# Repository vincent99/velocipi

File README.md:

# VelociPi

## About

This runs on a Raspberry Pi 5 to control the screens, cameras, joysticks, audio, and various other toys in my Velocity V-Twin-7 N711ME.

I don't know why you're here, but good luck.

## System setup

### Dependencies

These should be installed on the system:

```
sudo apt install chromium chromium-headless-shell ffmpeg mpv libchromaprint-tools
```

| Binary                           | Package                   | For                                                    |
| -------------------------------- | ------------------------- | ------------------------------------------------------ |
| `chromium-browser` or `chromium` | `chromium`                | Browser for local screen video streaming               |
| `chromium-headless-shell`        | `chromium-headless-shell` | Headless browser for OLED screen                       |
| `ffmpeg`                         | `ffmpeg`                  | DVR recording/streaming, music transcoding             |
| `ffprobe`                        | `ffmpeg`                  | Music duration/metadata extraction (comes with ffmpeg) |
| `mpv`                            | `mpv`                     | Music playback                                         |
| `fpcalc`                         | `libchromaprint-tools`    | Music fingerprinting (optional)                        |

### Hardware config

Enable I2C and SPI interfaces via `raspi-config` (Interface Options)

### Hiding the mouse cursor

Run this once to install a package that will hide the mouse cursor from the local screen

`sudo ./util/install-hideaway.sh`

## Dev

`npm run dev`

## Build

`npm run build`

## Configuration

See `config.yaml`

## WebSocket API

`/ws` carries JSON text frames in both directions (every message has a top-level `type` field). A separate `/screen` endpoint carries only binary PNG frames (the browser screencast) — no JSON messages.

Field-level types live in `ui/src/types/ws.ts` (frontend) and `server/messages.go` / the relevant subsystem's own `messages.go` (backend, e.g. `server/music/messages.go`, `server/dvr/dvr.go`) — this table is a human-readable index, not the source of truth. **Update this table whenever a message type is added, removed, renamed, or changes shape.**

### Server → client

| Type            | Key fields                                                                     | Description                                                       |
| --------------- | ------------------------------------------------------------------------------- | ------------------------------------------------------------------ |
| `ping`          | `time`                                                                           | Periodic heartbeat carrying the server's current time              |
| `airReading`    | `reading` (temp/pressure/humidity/dewpoint, °C+°F)                              | BME280 air sensor reading                                          |
| `luxReading`    | `lux`                                                                            | Ambient light sensor reading                                       |
| `tpms`          | `tire` (position, temp, pressure, voltage, battery, inflation/rotation state)   | One tire pressure sensor reading                                   |
| `ledState`      | `r`, `w`, `b`, `y` (each `{mode, rate?}`)                                        | Full state of all four expander LED channels                       |
| `keyEcho`       | `eventType`, `key`                                                               | Echoes a dispatched key event back to all clients, for UI feedback |
| `cameraStatus`  | `name`, `recording`                                                              | One camera's DVR recording status                                  |
| `recordingReady`| `camera`, `session`, `filename`                                                  | A DVR segment's thumbnails have finished generating                |
| `dvrState`      | `state` (`on`, `paused`, or `off`)                                               | Overall DVR recording state                                        |
| `diskSpace`     | `totalGB`, `usedGB`, `freeGB`, `usedPct`                                         | DVR storage disk space reading                                     |
| `localCamera`   | `camera`                                                                         | Camera currently shown on the local panel display                  |
| `axisState`     | `lat`, `lon`, `altFt`, `heading`, `roll`, `pitch`, `yaw`, `speedKts`, `oatCelsius`| Axis avionics state                                                 |
| `siyiAttitude`  | `camera`, `yaw`, `pitch`, `roll`, `yawRate`, `pitchRate`, `rollRate`             | Siyi gimbal attitude for one camera                                 |
| `musicState`    | `currentSongId`, `queueIndex`, `status`, `shuffle`, `repeat`, `elapsedSec`, `queueLength` | Music player state                                        |
| `musicQueue`    | `currentIndex`, `entries`                                                        | Full music queue snapshot                                          |
| `airConState`   | `state` (mode, fan, setpoint, temps, compressor, error, ...)                     | Aircon controller state                                             |
| `airConHistory` | `history` (array of temp samples)                                               | Temperature history, sent to a client on connect                    |
| `airConSample`  | `sample`                                                                         | One new temperature sample                                          |
| `btDevices`     | `devices` (address, name, paired, connected, trusted)                           | Known classic Bluetooth devices (paired + discovered)                |
| `btNowPlaying`  | `player` (track title/artist/album, status, position) or `null`                  | Current AVRCP now-playing metadata, `null` if no active session      |

### Client → server

| Type              | Key fields                                                  | Description                                                        |
| ----------------- | ------------------------------------------------------------ | -------------------------------------------------------------------- |
| `reload`          | —                                                              | Reload the chromedp browser page                                    |
| `key`             | `eventType`, `key`                                            | Dispatch a logical key event to chromedp / the expander input loop   |
| `led`             | `channel`, `state`, `rate?`                                   | Set one expander LED channel's state                                 |
| `navigate`        | `path`                                                         | Navigate the chromedp browser to a URL path                          |
| `setLocalCamera`  | `camera`                                                       | Change which camera is shown on the local panel display              |
| `musicControl`    | `action` (play/pause/stop/next/prev/seek/...), `value?`, `str?`| Control the music player                                            |
| `btControl`       | `action` (scan/pair/connect/.../playPause/next/previous), `address?` | Control Bluetooth device pairing (`btmedia`) or transport control (`bthid`) |

## Hardware

Display: Generic grayscale [SSD1322 OLED](https://www.amazon.com/dp/B0F7LBQM5N) module (256x64 assumed) or black & white [Noritake-Itron GE256X64B](https://www.noritake-elec.com/products/model?part=GE256X64B-7032B)
Joystick: [RKJXT1F42001](https://www.amazon.com/dp/B0DC623B3S) multi-function switch
Rotary encoder: [Dual concentric](https://www.propwashsim.com/store/p/dual-encoder-kit) with switch
I2C expander: [SX1509](https://www.adafruit.com/product/2260)
I2C air sensors: [BME280](https://www.adafruit.com/product/2652)
I2C light sensor: [VEML6030](https://www.adafruit.com/product/4396)

## Raspberry Pi GPIO pins

| BCM | Physical | Function  | Direction | Connected to                                                         |
| --- | -------- | --------- | --------- | -------------------------------------------------------------------- |
| 2   | 3        | I2C1 SDA  | Bidir     | SX1509 expander, BME280 air sensor, VEML6030 light sensor            |
| 3   | 5        | I2C1 SCL  | Output    | SX1509 expander, BME280 air sensor, VEML6030 light sensor            |
| 5   | 29       | Status/DC | In or Out | OLED status pin (SSD1327: D/C select output; GE256X64B: SBUSY input) |
| 6   | 31       | /RESET    | Output    | OLED reset (active low)                                              |
| 8   | 24       | SPI0 CE0  | Output    | OLED /CS                                                             |
| 10  | 19       | SPI0 MOSI | Output    | OLED data in                                                         |
| 11  | 23       | SPI0 SCLK | Output    | OLED clock                                                           |

I2C address defaults: expander `0x20`, air sensor `0x77`, light sensor `0x48`.
SPI0 port: `/dev/spidev0.0`, default clock `2.40 MHz`.

## SX1509 expander pins

The SX1509 is a 16-bit I2C GPIO expander (pins 0–15). All pins are inputs except the LED (pin 6, output).

| Pin | Function        | Notes                                     |
| --- | --------------- | ----------------------------------------- |
| 0   | Knob center     | Input, active low                         |
| 1   | Inner knob A    | Quadrature encoder (A/B pair with pin 2)  |
| 2   | Inner knob B    |                                           |
| 3   | Outer knob A    | Quadrature encoder (A/B pair with pin 4)  |
| 4   | Outer knob B    |                                           |
| 6   | LED             | Output                                    |
| 8   | Joystick center | Input, active low                         |
| 9   | Joystick down   | Input, active low                         |
| 10  | Joystick up     | Input, active low                         |
| 11  | Joystick right  | Input, active low                         |
| 12  | Joystick left   | Input, active low                         |
| 13  | Joy knob A      | Quadrature encoder (A/B pair with pin 14) |
| 14  | Joy knob B      |                                           |

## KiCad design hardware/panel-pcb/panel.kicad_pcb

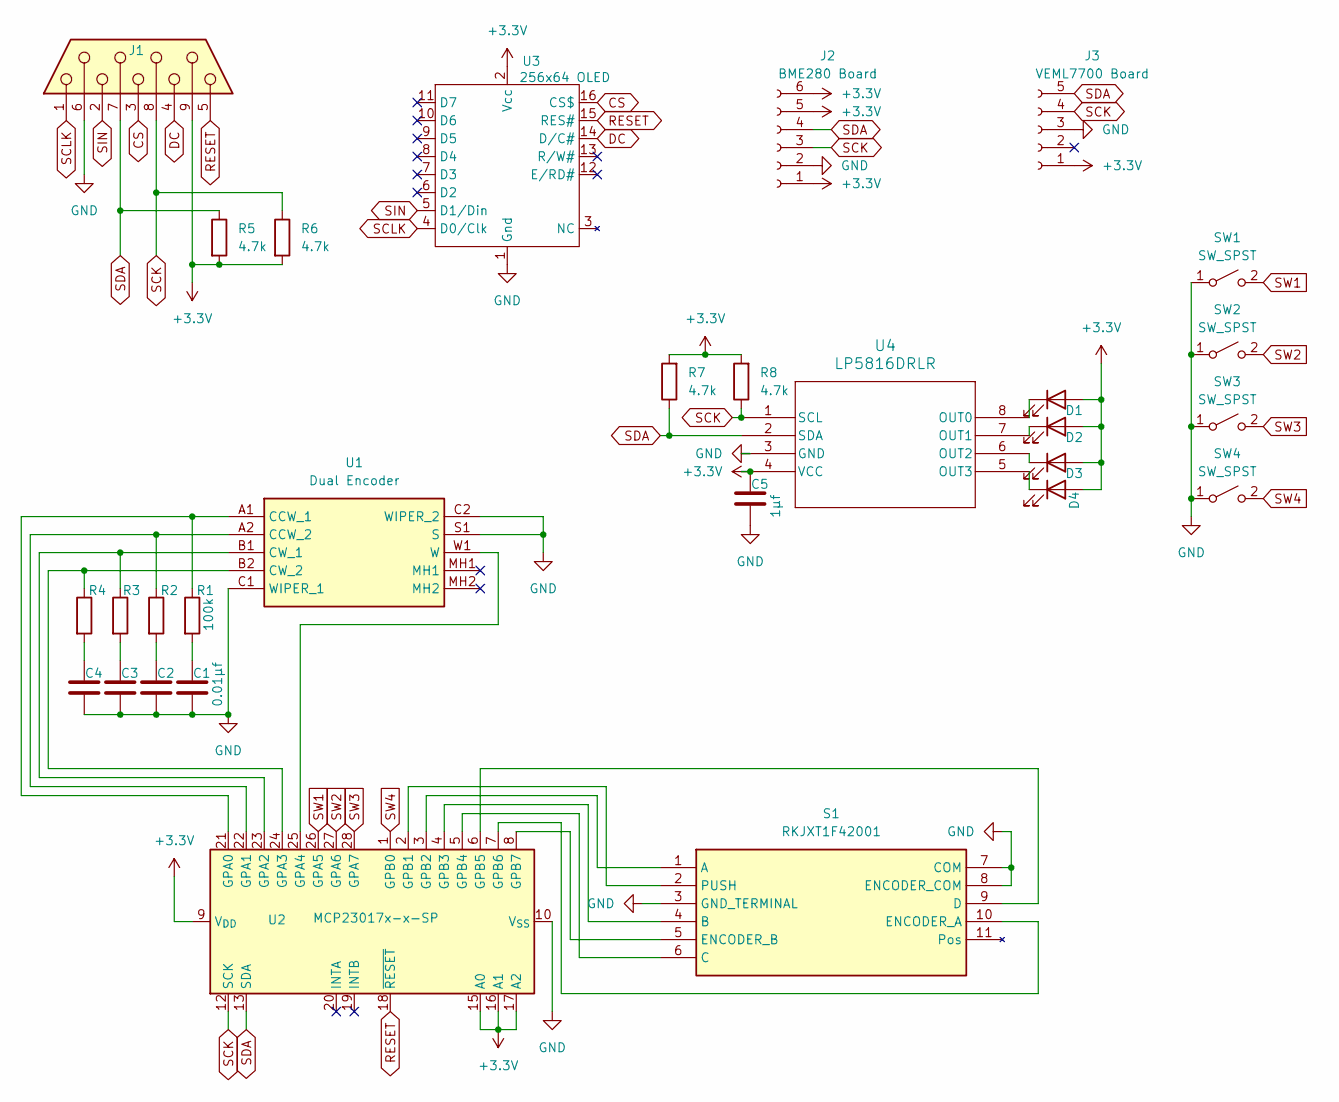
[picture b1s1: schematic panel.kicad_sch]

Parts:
C1, C2, C3, C4: 0.01µf; C_Disc_D5.0mm_W2.5mm_P5.00mm
C5: 1µf; C_Disc_D5.0mm_W2.5mm_P5.00mm
D1: Red; LED_D3.0mm
D2: White; LED_D3.0mm
D3: Blue; LED_D3.0mm
D4: Yellow; LED_D3.0mm
J1: DE9_Socket; DE9 Female
J2: BME280 Board
J3: VEML7700 Board
R1, R2, R3, R4: 100k; R_Axial_DIN0207_L6.3mm_D2.5mm_P7.62mm_Horizontal
R5, R6, R7, R8: 4.7k; R_Axial_DIN0207_L6.3mm_D2.5mm_P7.62mm_Horizontal
S1: RKJXT1F42001; Manufacturer_Part_Number RKJXT1F42001; Mouser Part Number 688-RKJXT1F42001
SW1, SW2, SW3, SW4: SW_SPST; SW_PUSH_6mm_H8mm
U1: Dual Encoder; PEC11D4120FH0015; Mouser Part Number 652-PEC11D4120FH0015
U2: MCP23017x-x-SP; DIP-28_W7.62mm
U3: 256x64 OLED; 3_12_OLED
U4: LP5816DRLR

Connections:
+3.3V: C5.1, D1.2 (A), D2.2 (A), D3.2 (A), D4.2 (A), J1.9, J2.1, J2.5, J2.6, J3.1, R5.2, R6.2, R7.2, R8.2, U2.9 (V_{DD}), U2.15 (A0), U2.16 (A1), U2.17 (A2), U3.2 (Vcc), U4.4 (VCC)
CS: J1.3, U3.16 (CS$)
DC: J1.4, U3.14 (D/C#)
GND: C1.2, C2.2, C3.2, C4.2, C5.2, J1.6, J2.2, J3.3, S1.3 (GND_TERMINAL), S1.7 (COM), S1.8 (ENCODER_COM), SW1.1 (A), SW2.1 (A), SW3.1 (A), SW4.1 (A), U1.C1 (WIPER_1), U1.C2 (WIPER_2), U1.S1 (S), U2.10 (V_{SS}), U3.1 (Gnd), U4.3 (GND)
unnamed: C1.1, R1.2
unnamed: C2.1, R2.2
unnamed: C3.1, R3.2
unnamed: C4.1, R4.2
unnamed: D1.1 (K), U4.8 (OUT0)
unnamed: D2.1 (K), U4.7 (OUT1)
unnamed: D3.1 (K), U4.6 (OUT2)
unnamed: D4.1 (K), U4.5 (OUT3)
unnamed: S1.1 (A), U2.3 (GPB2)
unnamed: S1.4 (B), U2.4 (GPB3)
unnamed: S1.6 (C), U2.5 (GPB4)
unnamed: S1.9 (D), U2.6 (GPB5)
unnamed: S1.10 (ENCODER_A), U2.7 (GPB6)
unnamed: S1.5 (ENCODER_B), U2.8 (GPB7)
unnamed: S1.2 (PUSH), U2.2 (GPB1)
unnamed: R1.1, U1.A1 (CCW_1), U2.21 (GPA0)
unnamed: R2.1, U1.A2 (CCW_2), U2.22 (GPA1)
unnamed: R3.1, U1.B1 (CW_1), U2.23 (GPA2)
unnamed: R4.1, U1.B2 (CW_2), U2.24 (GPA3)
unnamed: U1.W1 (W), U2.25 (GPA4)
RESET: J1.5, U2.18 (~RESET), U3.15 (RES#)
SCK: J1.8, J2.3, J3.4, R6.1, R8.1, U2.12 (SCK), U4.1 (SCL)
SCLK: J1.1, U3.4 (D0/Clk)
SDA: J1.7, J2.4, J3.5, R5.1, R7.1, U2.13 (SDA), U4.2 (SDA)
SIN: J1.2, U3.5 (D1/Din)
SW1: SW1.2 (B), U2.26 (GPA5)
SW2: SW2.2 (B), U2.27 (GPA6)
SW3: SW3.2 (B), U2.28 (GPA7)
SW4: SW4.2 (B), U2.1 (GPB0)

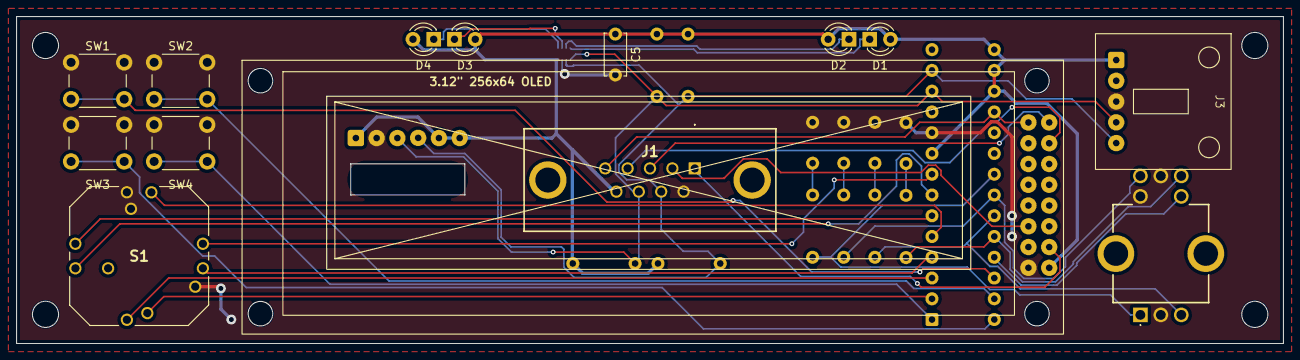
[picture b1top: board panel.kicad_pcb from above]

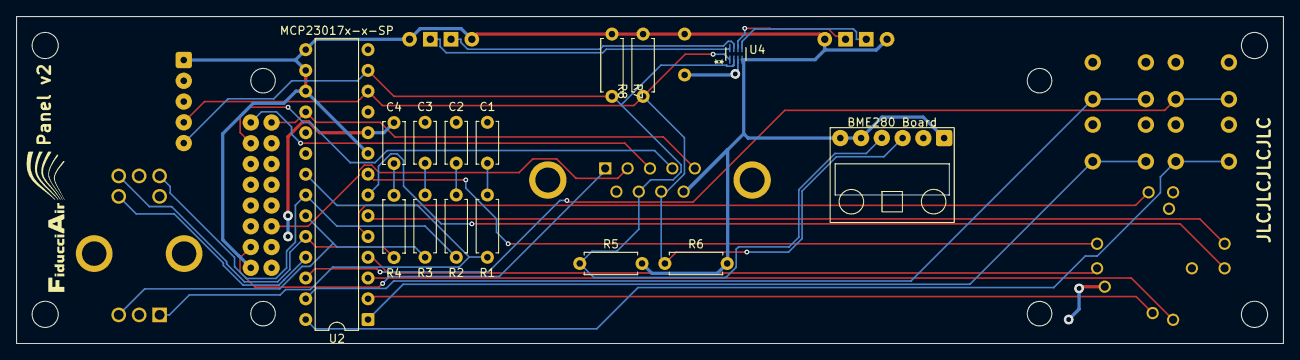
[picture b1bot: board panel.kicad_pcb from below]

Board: 2 copper layers, 155.0 x 40.0 mm, 33 parts (15 on the bottom side), 33 nets.

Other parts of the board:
MH1, MH2, MH3, MH4: MountingHole_3.2mm_M3

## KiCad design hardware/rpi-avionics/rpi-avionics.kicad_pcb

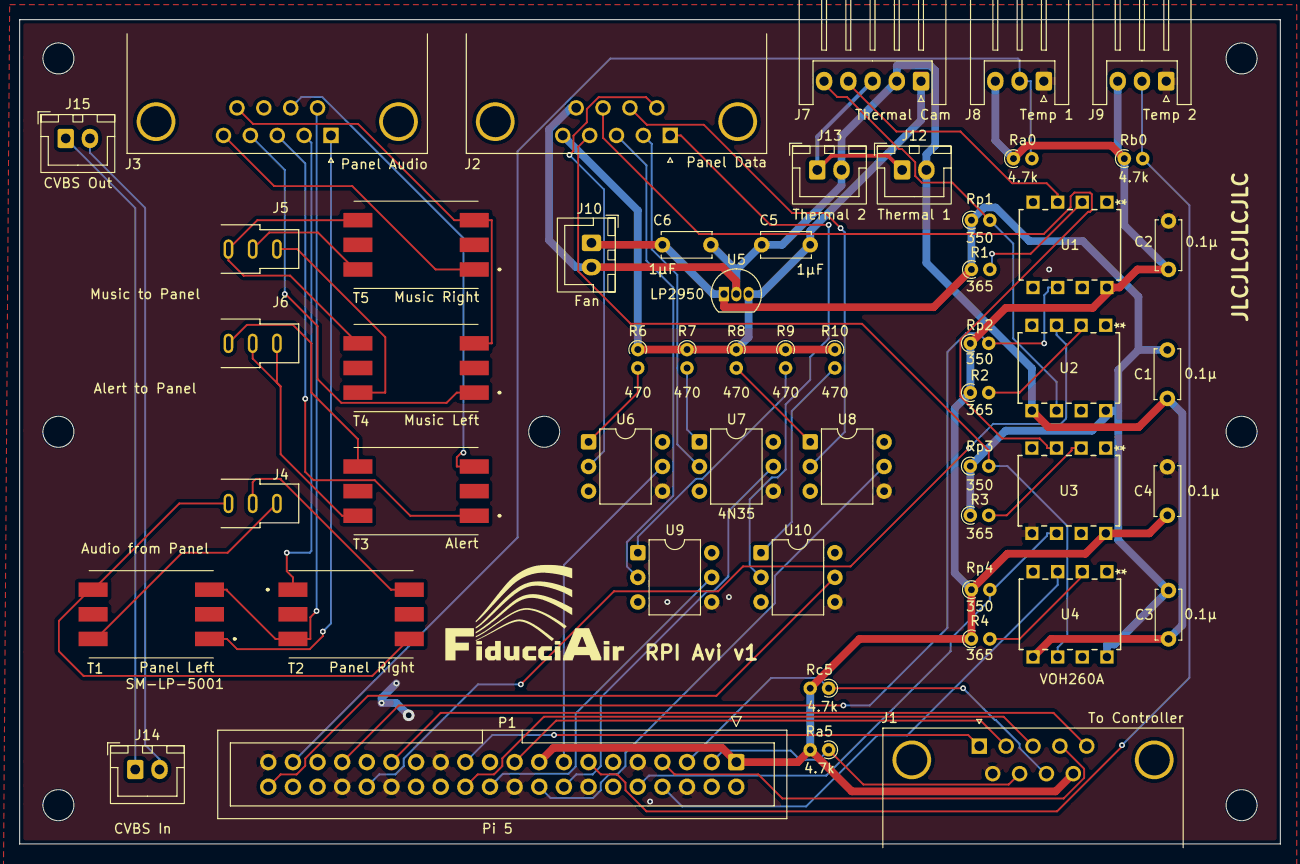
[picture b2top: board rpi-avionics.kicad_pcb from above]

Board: 2 copper layers, 130.0 x 85.0 mm, 60 parts (0 on the bottom side), 60 nets.

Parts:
C1, C2, C3, C4: 0.1µ; C_Disc_D5.0mm_W2.5mm_P5.00mm
C5, C6: 1µF; C_Disc_D5.0mm_W2.5mm_P5.00mm
J1: To Controller; DSUB-9_Pins_Horizontal_P2.77x2.84mm_EdgePinOffset7.70mm_Hou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
J2: Panel Data; DSUB-9_Pins_Horizontal_P2.77x2.84mm_EdgePinOffset7.70mm_Hou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
J3: Panel Audio; DSUB-9_Pins_Horizontal_P2.77x2.84mm_EdgePinOffset7.70mm_Hou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
J4: Audio from Panel; TENSILITY_54-00036
J5: Music to Panel; TENSILITY_54-00036
J6: Alert to Panel; TENSILITY_54-00036
J7: Thermal Cam; JST_XH_S5B-XH-A_1x05_P2.50mm_Horizontal
J8: Temp 1; JST_XH_S3B-XH-A_1x03_P2.50mm_Horizontal
J9: Temp 2; JST_XH_S3B-XH-A_1x03_P2.50mm_Horizontal
J10: Fan; JST_XH_B2B-XH-A_1x02_P2.50mm_Vertical
J12: Thermal 1; JST_XH_B2B-XH-A_1x02_P2.50mm_Vertical
J13: Thermal 2; JST_XH_B2B-XH-A_1x02_P2.50mm_Vertical
J14: CVBS In; JST_XH_B2B-XH-A_1x02_P2.50mm_Vertical
J15: CVBS Out; JST_XH_B2B-XH-A_1x02_P2.50mm_Vertical
MH1, MH2, MH3, MH4, MH5, MH6, MH7: MountingHole_3.2mm_M3
P1: Pi 5; IDC-Header_2x20_P2.54mm_Vertical
R1, R2, R3, R4: 365; R_Axial_DIN0204_L3.6mm_D1.6mm_P1.90mm_Vertical
R6, R7, R8, R9, R10: 470; R_Axial_DIN0204_L3.6mm_D1.6mm_P1.90mm_Vertical
Ra0, Ra5: 4.7k; R_Axial_DIN0204_L3.6mm_D1.6mm_P1.90mm_Vertical
Rb0: 4.7k; R_Axial_DIN0204_L3.6mm_D1.6mm_P1.90mm_Vertical
Rc5: 4.7k; R_Axial_DIN0204_L3.6mm_D1.6mm_P1.90mm_Vertical
Rp1, Rp2, Rp3, Rp4: 350; R_Axial_DIN0204_L3.6mm_D1.6mm_P1.90mm_Vertical
T1: Panel Left; SMLP5001
T2: Panel Right; SMLP5001
T3: Alert; SMLP5001
T4: Music Left; SMLP5001
T5: Music Right; SMLP5001
U1, U2, U3, U4: VOH260A; VOH263A_DIP8
U5: LP2950; TO-92_Inline
U6, U7, U8, U9, U10: 4N35; DIP-6_W7.62mm

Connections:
+3.3V: C2.1, C4.1, J1.9, J8.3, J9.3, P1.1 (3V3), P1.17 (3V3), R2.1, R4.1, Ra0.1, Ra5.2, Rb0.1, Rc5.2, Rp2.1, Rp4.1, U1.8 (VCC), U3.8 (VCC)
+12V: C5.1, J2.5, J7.1, R6.1, R7.1, R8.1, R9.1, R10.1, U5.3 (VI)
ALERT_HI: J3.3, T3.1 (PRI_1)
ALERT_LO: J3.7, T3.3 (PRI_2)
GARMIN_G3X_RX: J2.4, Rp3.2, U4.6 (VO)
GARMIN_G3X_TX: J2.8, U3.3 (CATHODE)
GARMIN_IO21: J2.1, U10.2
GARMIN_IO22: J2.6, U6.2
GARMIN_IO23: J2.2, U7.2
GARMIN_IO24: J2.7, U8.2
GARMIN_IO25: J2.3, U9.2
GARMIN_PI_RX: P1.10 (GPIO15/UART_RXD), Rp4.2, U3.6 (VO)
GARMIN_PI_TX: P1.8 (GPIO14/UART_TXD), U4.3 (CATHODE)
GND: C2.2, C4.2, J1.6, J8.1, J9.1, P1.6 (GND), P1.9 (GND), P1.14 (GND), P1.20 (GND), P1.25 (GND), P1.30 (GND), P1.34 (GND), P1.39 (GND), U1.5 (GND), U3.5 (GND), U6.4, U7.4, U8.4, U9.4, U10.4
GNDPWR: C1.1, C3.1, C5.2, C6.2, J2.9, J7.2, J10.2, J12.2, J13.2, U2.5 (GND), U4.5 (GND), U5.2 (GND)
I2C_SCK: J1.8, P1.5 (SCL_I2C1/GPIO03), Rc5.1
I2C_SDA: J1.7, P1.3 (SDA_I2C1/GPIO02), Ra5.1
IO21: P1.40 (GPIO21/SPI1_SCLK/PCM_DOUT), U10.5
IO22: P1.15 (GPIO22/SDIO_CLK), U6.5
IO23: P1.16 (GPIO23/SDIO_CMD), U7.5
IO24: P1.18 (GPIO24/SDIO_DAT0), U8.5
IO25: P1.22 (GPIO25/SDIO_DAT1), U9.5
MUSIC_C: J3.9, T4.3 (PRI_2), T5.3 (PRI_2)
MUSIC_L: J3.4, T4.1 (PRI_1)
MUSIC_R: J3.5, T5.1 (PRI_1)
unnamed: J14.1, J15.1
unnamed: J14.2, J15.2
unnamed: R6.2, U6.1
unnamed: R7.2, U7.1
unnamed: R8.2, U8.1
unnamed: R9.2, U9.1
unnamed: R10.2, U10.1
unnamed: J4.S, T1.4 (SEC_1), T2.4 (SEC_1)
unnamed: J4.T, T1.6 (SEC_2)
unnamed: J4.R, T2.6 (SEC_2)
unnamed: J6.S, T3.4 (SEC_1)
unnamed: J6.R, J6.T, T3.6 (SEC_2)
unnamed: J5.S, T4.4 (SEC_1), T5.4 (SEC_1)
unnamed: J5.T, T4.6 (SEC_2)
unnamed: J5.R, T5.6 (SEC_2)
unnamed: R1.2, U1.2 (ANODE)
unnamed: R2.2, U2.2 (ANODE)
unnamed: R3.2, U3.2 (ANODE)
unnamed: R4.2, U4.2 (ANODE)
OLED_CS: J1.3, P1.24 (~CE0_SPI0/GPIO08)
OLED_DC: J1.4, P1.7 (GPCLK0/GPIO04)
OLED_SCLK: J1.1, P1.23 (SCLK_SPI0/GPIO11)
OLED_SIN: J1.2, P1.19 (MOSI_SPI0/GPIO10)
PANEL_C: J3.6, T1.3 (PRI_2), T2.3 (PRI_2)
PANEL_L: J3.1, T1.1 (PRI_1)
PANEL_R: J3.2, T2.1 (PRI_1)
RESET: J1.5, P1.29 (GPCLK1/GPIO05)
TEMP1: J8.2, P1.37 (GPIO26/SDIO_DAT2), Ra0.2
TEMP2: J9.2, P1.13 (GPIO27/SDIO_DAT3), Rb0.2
VCC: C1.2, C3.2, C6.1, J10.1, R1.1, R3.1, Rp1.1, Rp3.1, U2.8 (VCC), U4.8 (VCC), U5.1 (VO)
VIDEO: J7.3, J12.1, J13.1
VIDEO_CAM_RX: J7.5, Rp1.2, U2.6 (VO)
VIDEO_CAM_TX: J7.4, U1.3 (CATHODE)
VIDEO_PI_RX: P1.33 (GPIO13/PWM1/UART4_RXD), Rp2.2, U1.6 (VO)
VIDEO_PI_TX: P1.32 (GPIO12/PWM0/UART4_TXT), U2.3 (CATHODE)

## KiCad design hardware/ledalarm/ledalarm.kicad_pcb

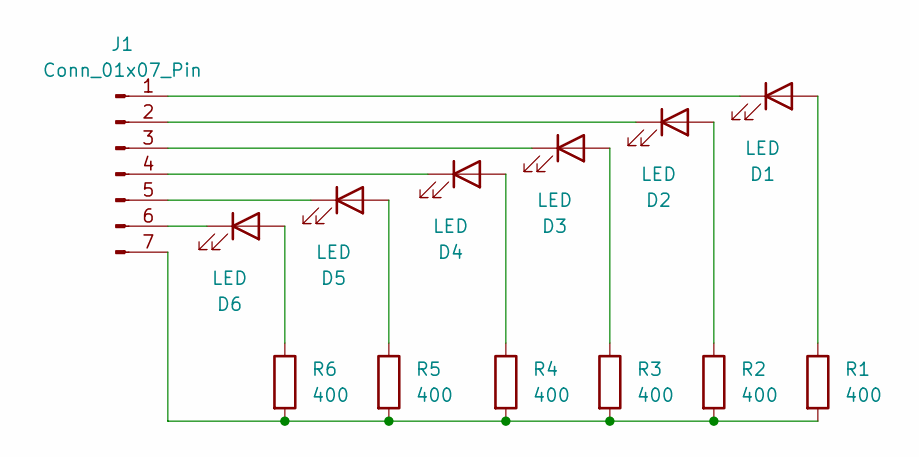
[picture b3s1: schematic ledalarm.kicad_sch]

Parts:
D1, D2, D3, D4, D5, D6: LED; LED_D5.0mm
J1: Conn_01x07_Pin; JST_XH_B7B-XH-A_1x07_P2.50mm_Vertical
R1, R2, R3, R4, R5, R6: 400; R_Axial_DIN0207_L6.3mm_D2.5mm_P10.16mm_Horizontal

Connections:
unnamed: D1.2 (A), R1.1
unnamed: D1.1 (K), J1.1
unnamed: D2.2 (A), R2.1
unnamed: D2.1 (K), J1.2
unnamed: D3.2 (A), R3.1
unnamed: D3.1 (K), J1.3
unnamed: D4.2 (A), R4.1
unnamed: D4.1 (K), J1.4
unnamed: D5.2 (A), R5.1
unnamed: D5.1 (K), J1.5
unnamed: D6.2 (A), R6.1
unnamed: D6.1 (K), J1.6
unnamed: J1.7, R1.2, R2.2, R3.2, R4.2, R5.2, R6.2

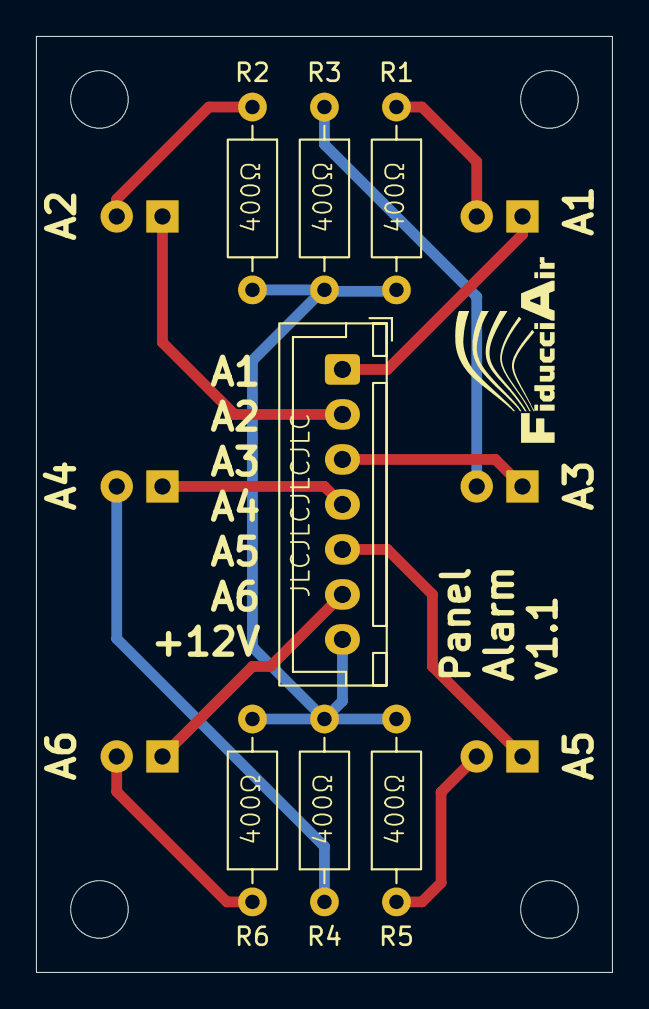
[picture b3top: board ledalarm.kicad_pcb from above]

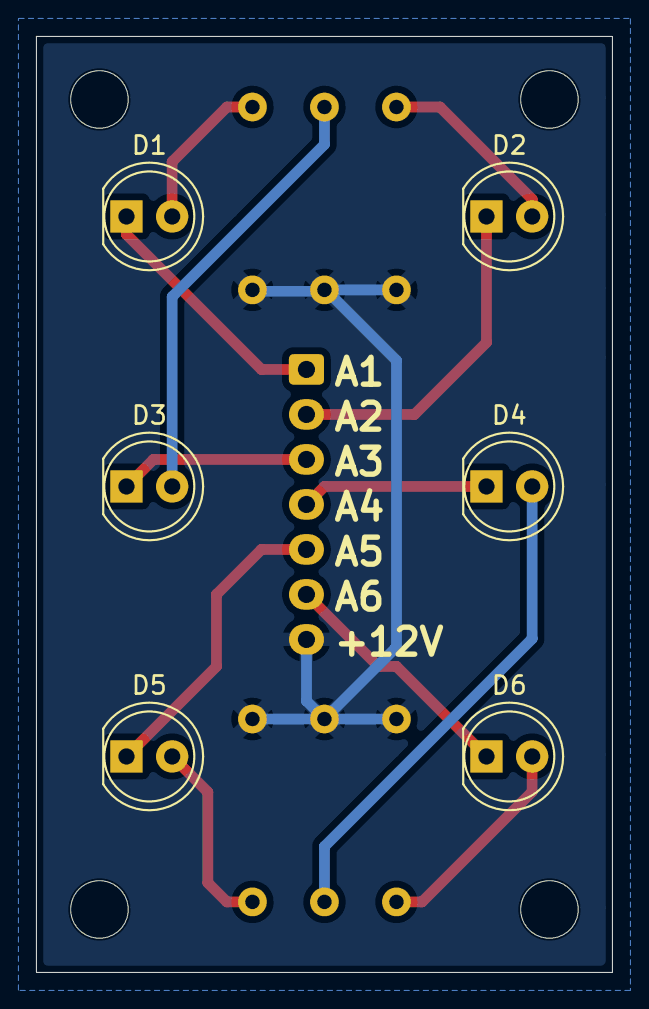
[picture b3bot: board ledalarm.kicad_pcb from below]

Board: 4 copper layers, 32.0 x 52.0 mm, 13 parts (6 on the bottom side), 13 nets.

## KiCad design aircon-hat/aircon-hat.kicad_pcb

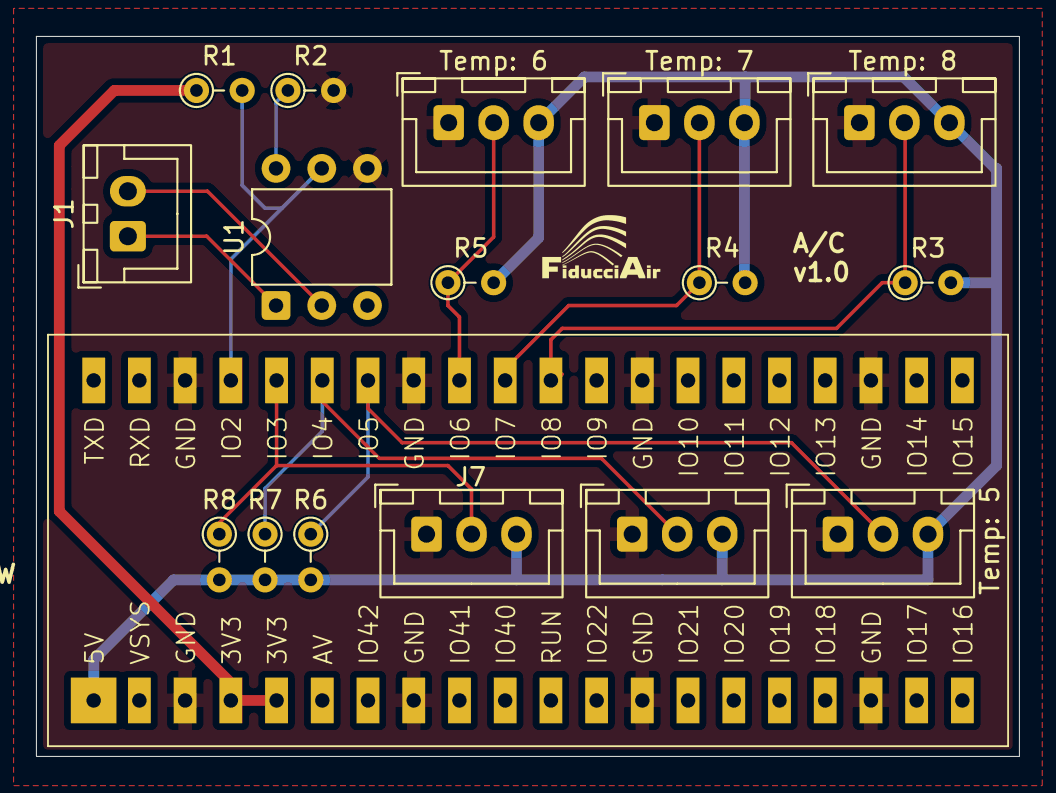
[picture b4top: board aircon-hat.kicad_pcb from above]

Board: 2 copper layers, 54.6 x 40.0 mm, 17 parts (0 on the bottom side), 13 nets.

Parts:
J1: PWM2; JST_XH_B2B-XH-A_1x02_P2.50mm_Vertical
J2: Temp: 8; JST_XH_B3B-XH-A_1x03_P2.50mm_Vertical
J3: Temp: 7; JST_XH_B3B-XH-A_1x03_P2.50mm_Vertical
J4: Temp: 6; JST_XH_B3B-XH-A_1x03_P2.50mm_Vertical
J5: Temp: 5; JST_XH_B3B-XH-A_1x03_P2.50mm_Vertical
J6: Temp4; JST_XH_B3B-XH-A_1x03_P2.50mm_Vertical
J7: Temp3; JST_XH_B3B-XH-A_1x03_P2.50mm_Vertical
R1: 10k; R_Axial_DIN0204_L3.6mm_D1.6mm_P2.54mm_Vertical
R2: 100k; R_Axial_DIN0204_L3.6mm_D1.6mm_P2.54mm_Vertical
R3, R4, R5, R6, R7, R8: 4.7k; R_Axial_DIN0204_L3.6mm_D1.6mm_P2.54mm_Vertical
RP2350-Relay-6CH-W1: RP2350-Relay-6CH-W
U1: 4N35; DIP-6_W7.62mm

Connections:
+3.3V: R1.1, RP2350-Relay-6CH-W1.4 (3V3), RP2350-Relay-6CH-W1.5 (3V3)
+5V: J2.3, J3.3, J4.3, J5.3, J6.3, J7.3, R3.2, R4.2, R5.2, R6.2, R7.2, R8.2, RP2350-Relay-6CH-W1.1 (+5V)
GND: J2.1, J3.1, J4.1, J5.1, J6.1, J7.1, R2.2, RP2350-Relay-6CH-W1.3 (GND), RP2350-Relay-6CH-W1.8 (GND), RP2350-Relay-6CH-W1.13 (GND), RP2350-Relay-6CH-W1.18 (GND), RP2350-Relay-6CH-W1.23 (GND), RP2350-Relay-6CH-W1.28 (GND), RP2350-Relay-6CH-W1.33 (GND), RP2350-Relay-6CH-W1.38 (GND), U1.4
unnamed: J1.1, U1.1
unnamed: J1.2, U1.2
unnamed: J2.2, R3.1, RP2350-Relay-6CH-W1.30 (IO8)
unnamed: J3.2, R4.1, RP2350-Relay-6CH-W1.31 (IO7)
unnamed: J4.2, R5.1, RP2350-Relay-6CH-W1.32 (IO6)
unnamed: J5.2, R6.1, RP2350-Relay-6CH-W1.34 (IO5)
unnamed: J6.2, R7.1, RP2350-Relay-6CH-W1.35 (IO4)
unnamed: J7.2, R8.1, RP2350-Relay-6CH-W1.36 (IO3)
unnamed: R2.1, U1.6
unnamed: R1.2, RP2350-Relay-6CH-W1.37 (IO2), U1.5

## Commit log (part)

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2025-07-25 Wails skeleton, I2C lib, Ambient light sensor
2025-08-01 LCD brightness, IO expander
2025-10-28 Start Wave3 support
2025-10-28 Auto brightness
2025-10-28 TPMS
2025-10-29 More tpms addresses
2025-11-01 Smoother brightness adjustment
2025-11-01 Air sensor, tpms bits
2025-11-05 Sensors
2025-11-05 ElementPlus
2025-12-12 Air and light sensor, routes
2025-12-12 Fix pixel order
2026-01-06 Window renderer
2026-01-07 Joystick and Knob events
2026-02-18 Hardware moldules
2026-02-19 Air sensor
2026-02-19 Key events
2026-02-19 Faster screen scraping
2026-02-19 Rotary encoders
2026-02-19 Splash screen
2026-02-19 Load URL in chromedp, clean shutdown
2026-02-20 Move UI to Vue
2026-02-20 Reorganize server code, shared config.yaml
2026-02-20 Move config stuff to yaml
2026-02-20 Move vue to 8081
2026-02-20 Save last frame to send to new clients
2026-02-20 Update key event names
2026-02-20 admin->remote, app->panel
2026-02-20 Remove duplicate defaults
2026-02-20 Path-based routing
2026-02-20 Key relay on panels
2026-02-20 eslint/prettier
2026-02-20 Move keyrelay
2026-02-20 NavMenu
2026-02-20 Navmenu and keyboard events
2026-02-20 Home and Kbd panels
2026-02-20 More routes
2026-02-20 SCSS
2026-02-21 Disconnected red X
2026-02-21 @ for includes
2026-02-21 Virtual panel
2026-02-21 Key events, virtual panel
2026-02-21 Config page
2026-02-21 Settings page, restore defaults
2026-02-21 Lint
2026-02-21 Snapshots API
2026-02-21 Cameras in header
2026-02-21 Thumbnails in header
2026-02-21 Camera sorting
2026-02-21 Faster smaller thumbs with mixed-replace
2026-02-21 Buffering
2026-02-21 Lower latency video
2026-02-22 mpeg-ts streaming
2026-02-22 Reuse mpeg-ts stream
2026-02-22 Reorganize
2026-02-22 Recordings page
2026-02-22 Thumbnail timeout
2026-02-22 Icons
2026-02-22 Fix Safari live stream
2026-02-23 Small screen nav
2026-02-23 Local camera view on pi, panel control components
2026-02-23 Value panels, show times
2026-02-23 Panel bugs
2026-02-24 Noritake OLED support
2026-02-24 Session dir instead of date
2026-02-24 Style, virtual panel
2026-02-24 Fix recording rotation
2026-02-24 Dependabot
2026-02-24 Bump vue-router from 4.6.4 to 5.0.3 in /ui
    Bumps [vue-router](https://github.com/vuejs/router) from 4.6.4 to 5.0.3.
    - [Release notes](https://github.com/vuejs/router/releases)
    - [Commits](https://github.com/vuejs/router/compare/v4.6.4...v5.0.3)
    ---
    updated-dependencies:
    - dependency-name: vue-router
2026-02-24 Bump vue from 3.5.28 to 3.5.29 in /ui
    Bumps [vue](https://github.com/vuejs/core) from 3.5.28 to 3.5.29.
    - [Release notes](https://github.com/vuejs/core/releases)
    - [Changelog](https://github.com/vuejs/core/blob/main/CHANGELOG.md)
    - [Commits](https://github.com/vuejs/core/compare/v3.5.28...v3.5.29)
    ---
    updated-dependencies:
2026-02-24 Bump vue-tsc from 3.2.4 to 3.2.5 in /ui
    Bumps [vue-tsc](https://github.com/vuejs/language-tools/tree/HEAD/packages/tsc) from 3.2.4 to 3.2.5.
    - [Release notes](https://github.com/vuejs/language-tools/releases)
    - [Changelog](https://github.com/vuejs/language-tools/blob/master/CHANGELOG.md)
    - [Commits](https://github.com/vuejs/language-tools/commits/v3.2.5/packages/tsc)
    ---
    updated-dependencies:
2026-02-24 Bump @fontsource/roboto from 5.2.9 to 5.2.10 in /ui
    Bumps [@fontsource/roboto](https://github.com/fontsource/font-files/tree/HEAD/fonts/google/roboto) from 5.2.9 to 5.2.10.
    - [Changelog](https://github.com/fontsource/font-files/blob/main/CHANGELOG.md)
    - [Commits](https://github.com/fontsource/font-files/commits/HEAD/fonts/google/roboto)
    ---
    updated-dependencies:
    - dependency-name: "@fontsource/roboto"
2026-02-24 Bump eslint from 10.0.0 to 10.0.2 in /ui
    Bumps [eslint](https://github.com/eslint/eslint) from 10.0.0 to 10.0.2.
    - [Release notes](https://github.com/eslint/eslint/releases)
    - [Commits](https://github.com/eslint/eslint/compare/v10.0.0...v10.0.2)
    ---
    updated-dependencies:
    - dependency-name: eslint
2026-02-25 Restart stalled thumbnails
2026-02-25 Music player
2026-02-25 Music layouts
2026-02-25 Music features
2026-02-25 Play count
2026-02-26 Music API & routes
2026-02-26 Styling, music actions
2026-02-26 Favorites, playlists, smart searches
2026-02-26 Nav bugs
2026-02-26 Select music output device
2026-02-26 Flags component
2026-02-26 Move all song info to a store
2026-02-26 MusicBrainz lookup
2026-03-02 Recording stop/start, disk space monitoring and rolling off old files
2026-03-02 Reorganize music into smaller components
2026-03-02 Fix drag into queue
2026-03-02 BEtter touch support for iOS
2026-03-02 Start music panel
2026-03-05 Music and DVR bugs
2026-03-05 Siyi, pan/tilt/zoom support
2026-03-06 Lyrics support
2026-03-24 Bump github.com/chromedp/chromedp from 0.14.2 to 0.15.1
    Bumps [github.com/chromedp/chromedp](https://github.com/chromedp/chromedp) from 0.14.2 to 0.15.1.
    - [Release notes](https://github.com/chromedp/chromedp/releases)
    - [Commits](https://github.com/chromedp/chromedp/compare/v0.14.2...v0.15.1)
    ---
    updated-dependencies:
    - dependency-name: github.com/chromedp/chromedp
2026-03-25 Music lyrics, queue undo
2026-04-03 Music reorganization, features
2026-04-03 Air conditioner controller RPI pico
2026-04-03 Reorganize queueing, add insert
2026-04-03 action menus on remote screens
2026-04-07 rp2350 docs
2026-04-07 LED alarm board
2026-04-07 Connect to actual rp2350, bluetooth control
2026-04-07 Async connect to wifi, reconnect on failure
2026-04-07 Max -> Cool
2026-04-07 NTP time
2026-04-07 Use relay for fresh/recirc
2026-04-09 AirCon BLE config, LED panel, controller hat
2026-04-10 Final aircon hat, handle soft-reset better
2026-04-10 UI style
2026-04-10 AC remote and panel UIs
2026-04-10 AirCon config in settings
2026-04-10 Include circ mode in startup msg
2026-04-10 Move hardware projects
2026-04-10 Fix ble scanner
2026-04-10 Move all music/recordings/dbs/etc into data
2026-04-10 Handle bigger BLE aircon config/status
2026-04-10 Optional BLE notify, reorg startup
2026-04-13 Move aircon files around
2026-04-13 More aircon hardware
2026-04-14 Bump periph.io/x/conn/v3 from 3.7.2 to 3.7.3
    Bumps [periph.io/x/conn/v3](https://github.com/periph/conn) from 3.7.2 to 3.7.3.
    - [Release notes](https://github.com/periph/conn/releases)
    - [Commits](https://github.com/periph/conn/compare/v3.7.2...v3.7.3)
    ---
    updated-dependencies:
    - dependency-name: periph.io/x/conn/v3
2026-04-20 Slider, AP mode with no gateway
2026-04-21 Bump tinygo.org/x/bluetooth from 0.14.0 to 0.15.0
    Bumps [tinygo.org/x/bluetooth](https://github.com/tinygo-org/bluetooth) from 0.14.0 to 0.15.0.
    - [Release notes](https://github.com/tinygo-org/bluetooth/releases)
    - [Changelog](https://github.com/tinygo-org/bluetooth/blob/dev/CHANGELOG.md)
    - [Commits](https://github.com/tinygo-org/bluetooth/compare/v0.14.0...v0.15.0)
    ---
    updated-dependencies:
2026-04-22 Run on macos for dev, better debug page for state
2026-05-04 Run on macos, kicad files for hardware
2026-05-04 kicad for panel and avionics
2026-05-04 Drop unused fonts
2026-05-04 Thermal camera
2026-05-18 panel and avionics boards
2026-05-26 Panel v2
2026-05-26 Thermal cam client
2026-05-26 Update for PCB version of panel
